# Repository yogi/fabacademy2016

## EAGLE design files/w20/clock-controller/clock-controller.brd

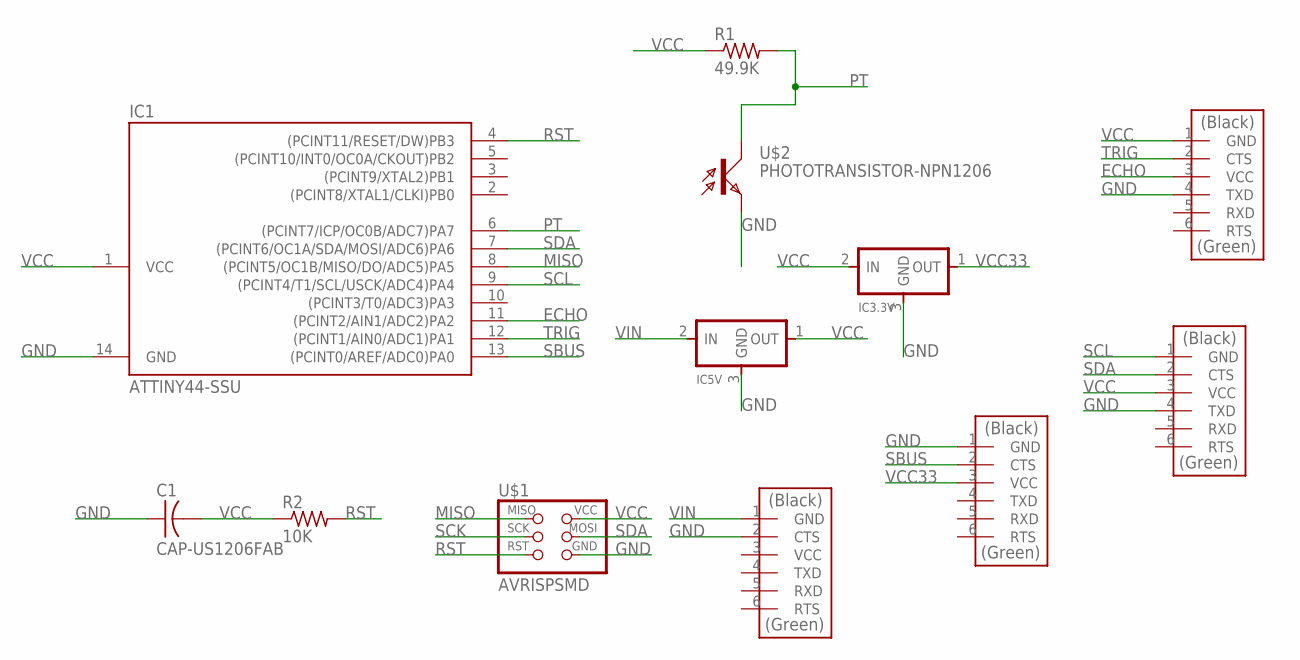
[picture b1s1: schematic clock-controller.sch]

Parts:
C1: CAP-US1206FAB; C1206FAB
DIGITS: FTDI-SMD-HEADER; 1X06SMD
IC1: ATTINY44-SSU; SOIC14
IC3.3V, IC5V: REGULATORSOT23; SOT23
R1: 49.9K; R1206FAB
R2: 10K; R1206FAB
RTC: FTDI-SMD-HEADER; 1X06SMD
U$1: AVRISPSMD; 2X03SMD
U$2: PHOTOTRANSISTOR-NPN1206; OP1206
ULTRA: FTDI-SMD-HEADER; 1X06SMD
USB: FTDI-SMD-HEADER; 1X06SMD

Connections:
ECHO: IC1.11 ((PCINT2/AIN1/ADC2)PA2), ULTRA.3 (VCC)
GND: C1.1, DIGITS.1 (GND), IC1.14 (GND), IC3.3V.3 (GND), IC5V.3 (GND), RTC.4 (TXD), U$1.6 (GND), U$2.EMITTER (E), ULTRA.4 (TXD), USB.2 (CTS)
MISO: IC1.8 ((PCINT5/OC1B/MISO/DO/ADC5)PA5), U$1.1 (MISO)
PT: IC1.6 ((PCINT7/ICP/OC0B/ADC7)PA7), R1.2, U$2.COLLECTOR (C)
RST: IC1.4 ((PCINT11/RESET/DW)PB3), R2.2, U$1.5 (RST)
SBUS: DIGITS.2 (CTS), IC1.13 ((PCINT0/AREF/ADC0)PA0)
SCK: U$1.3 (SCK)
SCL: IC1.9 ((PCINT4/T1/SCL/USCK/ADC4)PA4), RTC.1 (GND)
SDA: IC1.7 ((PCINT6/OC1A/SDA/MOSI/ADC6)PA6), RTC.2 (CTS), U$1.4 (MOSI)
TRIG: IC1.12 ((PCINT1/AIN0/ADC1)PA1), ULTRA.2 (CTS)
VCC: C1.2, IC1.1 (VCC), IC3.3V.2 (IN), IC5V.1 (OUT), R1.1, R2.1, RTC.3 (VCC), U$1.2 (VCC), ULTRA.1 (GND)
VCC33: DIGITS.3 (VCC), IC3.3V.1 (OUT)
VIN: IC5V.2 (IN), USB.1 (GND)

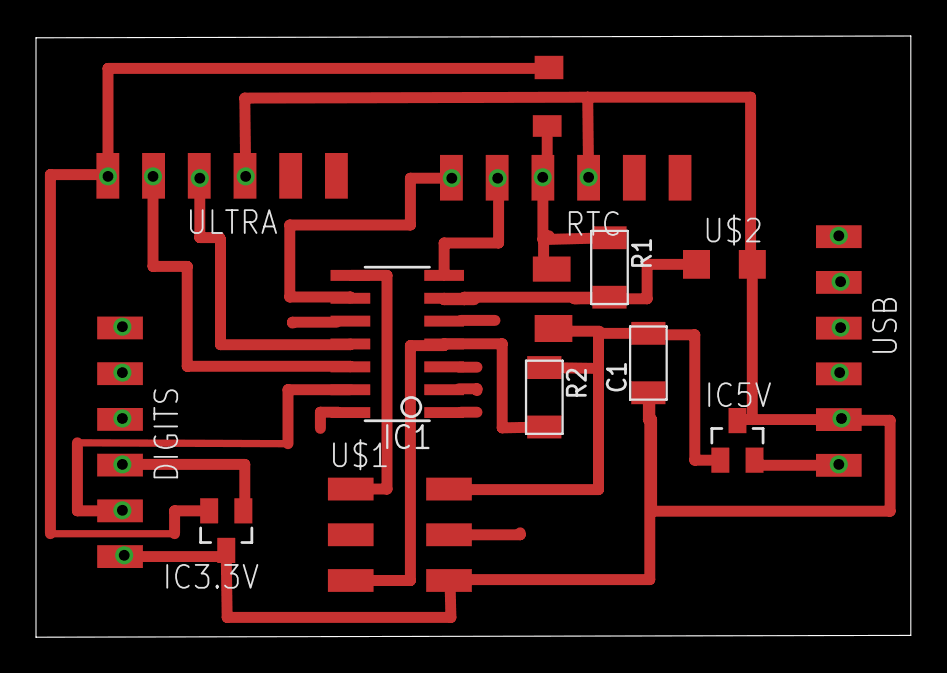
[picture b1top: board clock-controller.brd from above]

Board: 2 copper layers, 48.6 x 33.4 mm, 12 parts (0 on the bottom side), 12 nets.

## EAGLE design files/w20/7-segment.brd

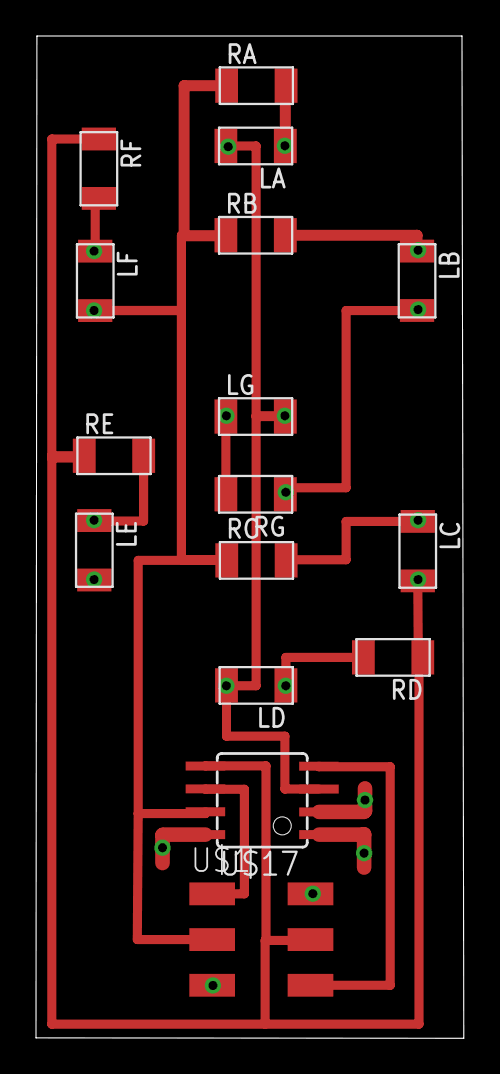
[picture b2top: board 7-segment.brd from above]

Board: 2 copper layers, 23.8 x 55.7 mm, 16 parts (0 on the bottom side), 15 nets.

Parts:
LA: LEDFAB1206; LED1206FAB
LB: LEDFAB1206; LED1206FAB
LC: LEDFAB1206; LED1206FAB
LD: LEDFAB1206; LED1206FAB
LE: LEDFAB1206; LED1206FAB
LF: LEDFAB1206; LED1206FAB
LG: LEDFAB1206; LED1206FAB
RA: R1206FAB
RB: R1206FAB
RC: R1206FAB
RD: R1206FAB
RE: R1206FAB
RF: R1206FAB
RG: R1206FAB
U$1: AVRISPSMD; 2X03SMD
U$17: ATTINY45SI; SOIC8

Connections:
GND: U$1.6, U$17.4
MISO: U$1.1, U$17.6
MOSI: LC.2, RD.1, RE.1, RF.1, U$1.4, U$17.5
unnamed: LA.1, RA.2
unnamed: LB.1, RB.2
unnamed: LC.1, RC.2
unnamed: LD.1, RD.2
unnamed: LE.1, RE.2
unnamed: LF.1, RF.2
unnamed: LG.1, RG.2
PB3: LB.2, LE.2, RG.1, U$17.2
PB4: LA.2, LD.2, LG.2, U$17.3
RST: U$1.5, U$17.1
SCK: LF.2, RA.1, RB.1, RC.1, U$1.3, U$17.7
VCC: U$1.2, U$17.8

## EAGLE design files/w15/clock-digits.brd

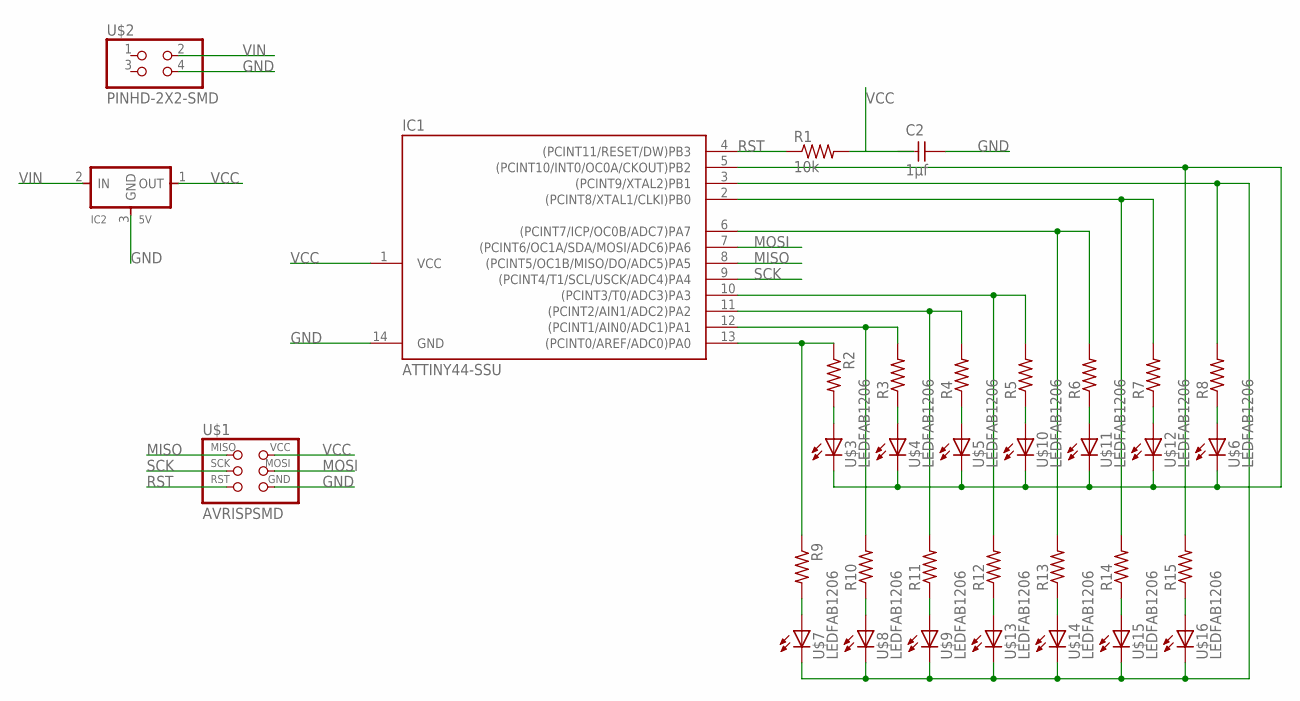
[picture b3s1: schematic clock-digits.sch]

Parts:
C2: 1µf; C1206FAB
IC1: ATTINY44-SSU; SOIC14
IC2: 5V; SOT23
R1: 10k; R1206FAB
R2, R3, R4, R5, R6, R7, R8, R9, R10, R11, R12, R13, R14, R15: RES-US1206FAB; R1206FAB
U$1: AVRISPSMD; 2X03SMD
U$2: PINHD-2X2-SMD; 2X02SMD
U$3, U$4, U$5, U$6, U$7, U$8, U$9, U$10, U$11, U$12, U$13, U$14, U$15, U$16: LEDFAB1206; LED1206FAB

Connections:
GND: C2.2, IC1.14 (GND), IC2.3 (GND), U$1.6 (GND), U$2.4
MISO: IC1.8 ((PCINT5/OC1B/MISO/DO/ADC5)PA5), U$1.1 (MISO)
MOSI: IC1.7 ((PCINT6/OC1A/SDA/MOSI/ADC6)PA6), U$1.4 (MOSI)
unnamed: IC1.13 ((PCINT0/AREF/ADC0)PA0), R2.1, R9.1
unnamed: R2.2, U$3.1 (A)
unnamed: IC1.12 ((PCINT1/AIN0/ADC1)PA1), R3.2, R10.2
unnamed: R3.1, U$4.1 (A)
unnamed: IC1.11 ((PCINT2/AIN1/ADC2)PA2), R4.2, R11.2
unnamed: R4.1, U$5.1 (A)
unnamed: IC1.10 ((PCINT3/T0/ADC3)PA3), R5.2, R12.2
unnamed: R5.1, U$10.1 (A)
unnamed: IC1.6 ((PCINT7/ICP/OC0B/ADC7)PA7), R6.2, R13.2
unnamed: R6.1, U$11.1 (A)
unnamed: IC1.2 ((PCINT8/XTAL1/CLKI)PB0), R7.2, R14.2
unnamed: R7.1, U$12.1 (A)
unnamed: R8.1, U$6.1 (A)
unnamed: IC1.5 ((PCINT10/INT0/OC0A/CKOUT)PB2), R15.2, U$3.2 (C), U$4.2 (C), U$5.2 (C), U$6.2 (C), U$10.2 (C), U$11.2 (C), U$12.2 (C)
unnamed: R9.2, U$7.1 (A)
unnamed: R15.1, U$16.1 (A)
unnamed: R10.1, U$8.1 (A)
unnamed: R11.1, U$9.1 (A)
unnamed: R12.1, U$13.1 (A)
unnamed: R13.1, U$14.1 (A)
unnamed: R14.1, U$15.1 (A)
unnamed: IC1.3 ((PCINT9/XTAL2)PB1), R8.2, U$7.2 (C), U$8.2 (C), U$9.2 (C), U$13.2 (C), U$14.2 (C), U$15.2 (C), U$16.2 (C)
RST: IC1.4 ((PCINT11/RESET/DW)PB3), R1.1, U$1.5 (RST)
SCK: IC1.9 ((PCINT4/T1/SCL/USCK/ADC4)PA4), U$1.3 (SCK)
VCC: C2.1, IC1.1 (VCC), IC2.1 (OUT), R1.2, U$1.2 (VCC)
VIN: IC2.2 (IN), U$2.2

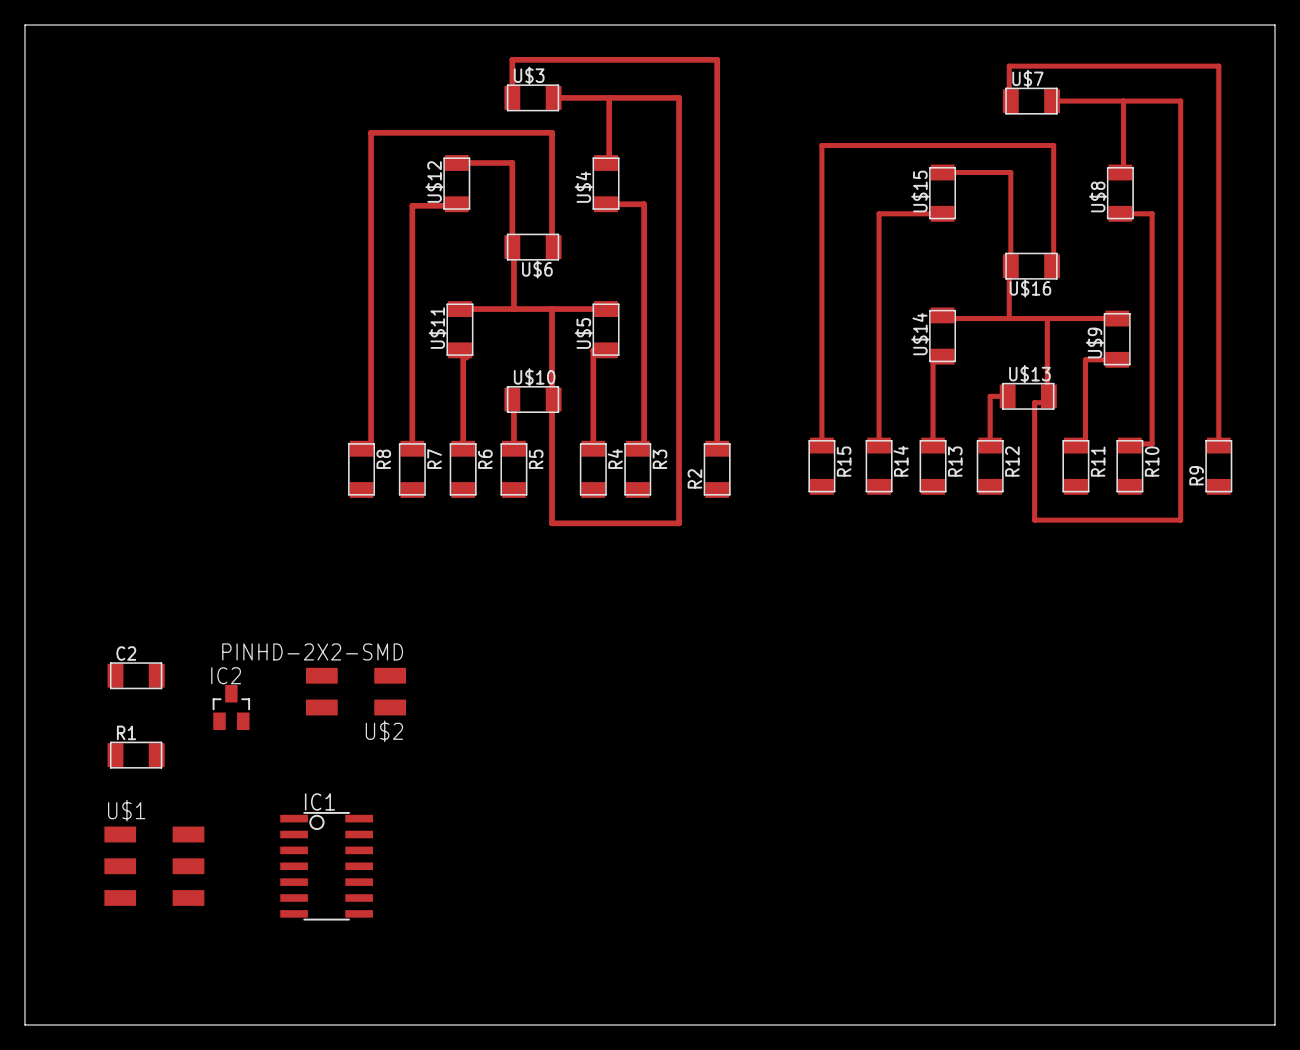
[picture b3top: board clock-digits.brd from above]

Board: 2 copper layers, 100.0 x 80.0 mm, 34 parts (0 on the bottom side), 29 nets.

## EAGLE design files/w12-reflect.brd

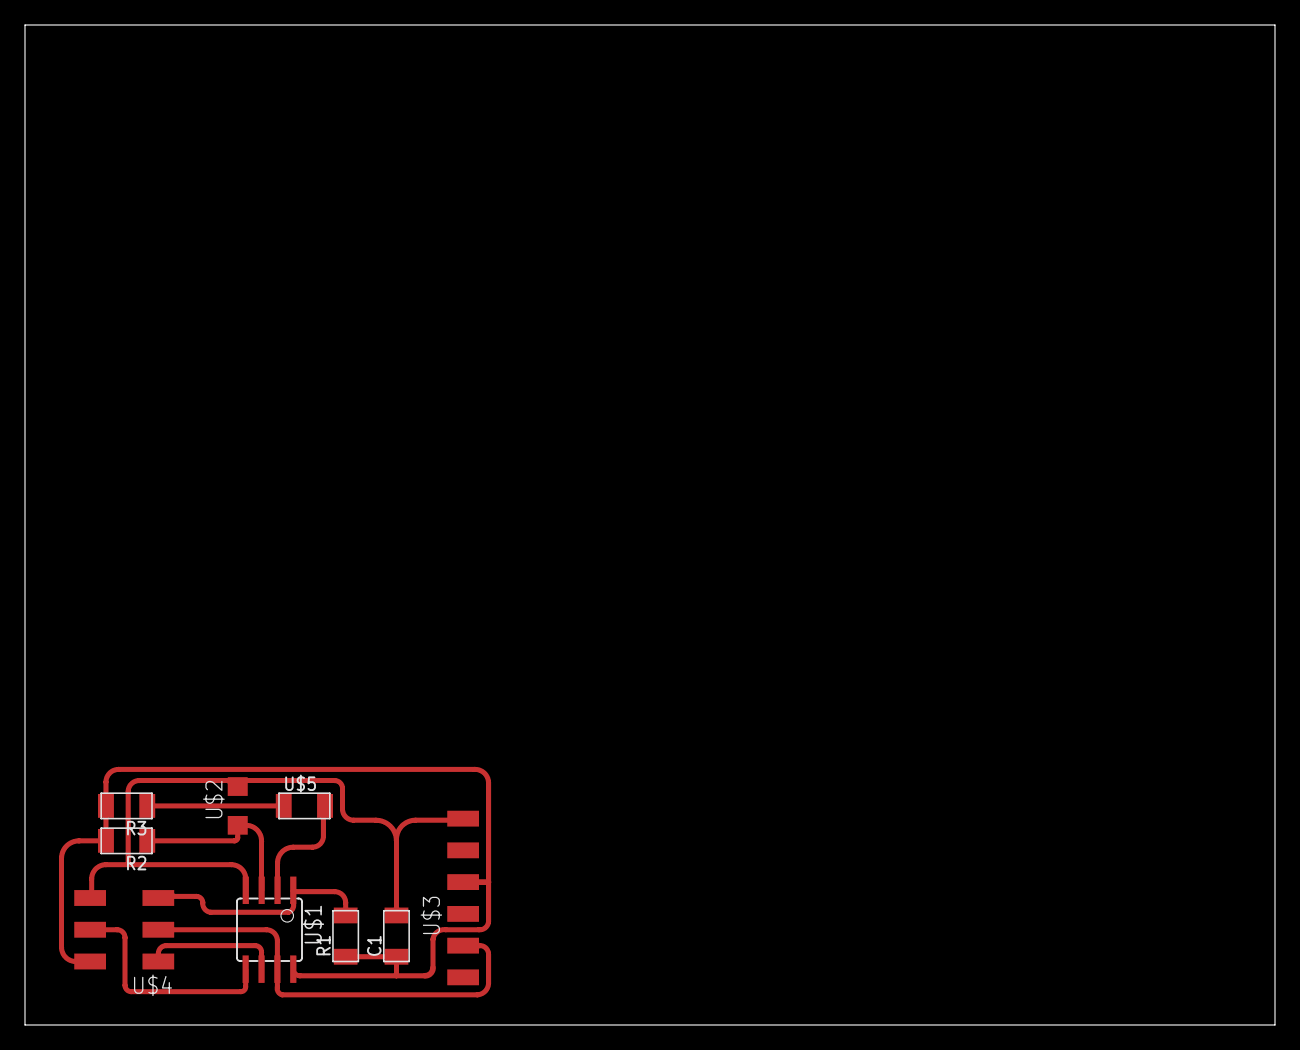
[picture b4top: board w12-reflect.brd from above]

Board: 2 copper layers, 100.0 x 80.0 mm, 9 parts (0 on the bottom side), 9 nets.

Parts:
C1: CAP-US1206FAB; C1206FAB
R1: 10k; R1206FAB
R2: 49.9k; R1206FAB
R3: 1k; R1206FAB
U$1: ATTINY45SI; SOIC8
U$2: PHOTOTRANSISTOR-NPN1206; OP1206
U$3: FTDI-SMD-HEADER; 1X06SMD
U$4: AVRISPSMD; 2X03SMD
U$5: LEDFAB1206; LED1206FAB

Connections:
GND: C1.2, U$1.4, U$2.EMITTER, U$3.1, U$4.6
LED: U$1.2, U$5.2
MISO: U$1.6, U$4.1
MOSI: U$1.5, U$4.4
unnamed: R3.1, U$5.1
PT: R2.1, U$1.3, U$2.COLLECTOR
RST: R1.2, U$1.1, U$4.5
SCK: U$1.7, U$3.5, U$4.3
VCC: C1.1, R1.1, R2.2, R3.2, U$1.8, U$3.3, U$4.2

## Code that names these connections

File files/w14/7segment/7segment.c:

#include <avr/io.h>
#include <util/delay.h>

#define SCK_PIN PB2
#define MOSI_PIN PB0

#define ABC_ANODE   SCK_PIN
#define A           PB4
#define B           PB3
#define C           MOSI_PIN

#define DEF_ANODE   MOSI_PIN
#define D           PB4
#define E           PB3
#define F           SCK_PIN

#define G_ANODE     PB3
#define G           PB4

#define DIR_REG   DDRB

#define output(pin) (DIR_REG |= (1 << pin)) // set port direction for output
#define input(pin) (DIR_REG &= (~ (1 << pin))) // set port direction for input
#define set(pin) (PORTB |= (1 << pin)) // set port pin
#define clear(pin) (PORTB &= (~ (1 << pin))) // clear port pin

const int FLICKER_DELAY_MS = 100;
const int DIGIT_DELAY_MS = 5000;

char DIGIT_SEGMENTS[10][7] = {
     {'A', 'B', 'C', 'D', 'E', 'F'},            // 0
     {'B', 'C'},                                // 1
     {'A', 'B', 'D', 'E', 'G'},                 // 2
     {'A', 'B', 'C', 'D', 'G'},                 // 3
     {'B', 'C', 'F', 'G'},                      // 4
     {'A', 'C', 'D', 'F', 'G'},                 // 5
     {'A', 'C', 'D', 'E', 'F', 'G'},            // 6
     {'A', 'B', 'C'},                           // 7
     {'A', 'B', 'C', 'D', 'E', 'F', 'G',},      // 8
     {'A', 'B', 'C', 'F', 'G',}                 // 9
};

int DIGIT_NUM_SEGMENTS[] = {
    6, // 0
    2, // 1
    5, // 2
    5, // 3
    4, // 4
    5, // 5
    6, // 6
    3, // 7
    7, // 8
    5  // 9
};

int anode_pin_for(char led) {
    if (led == 'A' || led == 'B' || led == 'C') 
        return ABC_ANODE;
    else if (led == 'D' || led == 'E' || led == 'F') 
        return DEF_ANODE;
    else  
        return G_ANODE;
}

int led_pin_for(char led) {
    if (led == 'A' || led == 'D' || led == 'G')
        return PB4;
    else if (led == 'B' || led == 'E')
        return PB3;
    else if (led == 'C')
        return MOSI_PIN;
    else // 'F'
        return SCK_PIN;
}

void high_impedance(pin) {
    input(pin);
    clear(pin);
}

void flash(char led) {
    int anode_pin = anode_pin_for(led);
    int led_pin = led_pin_for(led);
    
    output(anode_pin);    
    output(led_pin);
        
    set(anode_pin);
    clear(led_pin);

    _delay_ms(FLICKER_DELAY_MS);
    
    high_impedance(anode_pin);    
    high_impedance(led_pin);
}

void flicker(char segments[]) {
    int i;
    int len = sizeof(segments) / sizeof(char);
    for (i = 0; i < len; i++) {
        flash(segments[i]);
    }
}

void display(int digit) {
    int i;
    char *segments = DIGIT_SEGMENTS[digit];
    int num_segments = DIGIT_NUM_SEGMENTS[digit];
//    int cycles = DIGIT_DELAY_MS / (FLICKER_DELAY_MS * num_segments);
    int cycles = DIGIT_DELAY_MS / (FLICKER_DELAY_MS * 2);
    for (i = 0; i < cycles; i++) {
        flicker(segments);
    }
}

/*
int main(void) {
    high_impedance(PB0);
    high_impedance(PB1);
    high_impedance(PB2);
    high_impedance(PB3);
    high_impedance(PB4);

    int i = 0;
    while(1) {
        display(i); 
        if (++i >= 10)
            i = 0;
    }
    
    return 0;
}
*/


int main(void) {
    char leds[] = {'A', 'B', 'C', 'D', 'E', 'F', 'G'};
    int i = 0;
    
    while(1) {
        flash(leds[i++]);
        _delay_ms(100);
        if (i >= 7)
            i = 0;
    }
    
    return 0;
}

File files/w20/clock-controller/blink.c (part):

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
#define digit_bus_port PORTA
#define digit_bus_direction DDRA
#define digit_bus_pin_out (1 << PA0)

#define serial_port PORTB
#define serial_direction DDRB
#define serial_pin_out (1 << PB2)

#define trigger_port PORTA
#define trigger_direction DDRA
#define trigger_pin_out (1 << PA1)

#define echo_port PORTA
#define echo_direction DDRA
#define echo_pin_in (1 << PA2)
#define echo_pins PINA

#define TURN_OFF_DISPLAY 11
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
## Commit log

2016-03-11 import from git.fabacademy.org
2016-03-11 add link in footer to site source on github
2016-03-14 machining notes
2016-03-14 table design in rhino
2016-03-14 zip 3dm file, which reduces size by 99%!
2016-03-14 fix zip folder
2016-03-14 zip big files
2016-03-15 scaled down model
2016-03-15 table done
2016-03-15 w8 page
2016-03-16 allowance offset note
2016-03-16 fix links
2016-03-17 w8 blink led
2016-03-17 update w4 notes
2016-03-17 update notes
2016-03-17 using my isp
2016-03-17 move blink.ino to its folder
2016-03-17 change title
2016-03-19 button + LED
2016-03-19 c blink led program
2016-03-20 c led program
2016-03-21 datasheet review notes
2016-03-21 fix headings
2016-03-21 assembler test
2016-03-21 original files links
2016-03-22 minor edits
2016-03-22 assembly blink program with delay
2016-03-22 program size comparisons
2016-03-22 interrupt-based program
2016-03-22 remove Todo
2016-03-23 polishing
2016-03-23 w10 page created
2016-03-23 floating menu
2016-03-23 intro
2016-03-23 about page
2016-03-29 timer blink
2016-03-29 tweaks
2016-03-29 refactor
2016-04-11 complete notes on uart
2016-04-11 remove *.elf and *.o files
2016-04-11 include uart section in index
2016-04-11 remove questions
2016-04-12 added w11 page
2016-04-15 fix machine index pic
2016-04-15 added combined machine page
2016-04-15 machine notes
2016-04-16 created w12-input
2016-04-17 schematic and board
2016-04-18 traces and outline png
2016-04-18 board done
2016-04-18 inputs hero shot
2016-04-20 theme refactoring - index page done
2016-04-20 theme refactoring - fix navbar
2016-04-20 index re-theming done
2016-04-20 footer
2016-04-22 fix format errors on all pages
2016-04-22 change navbar text color
2016-04-22 add photo
2016-04-22 fix layout
2016-04-22 minor tweaks to fabacademy page
2016-04-22 fix link
2016-04-25 added w13 page, fixed navbar toggle for small screens
2016-04-26 spirograph rhino design
2016-04-26 spirograph mold designs
2016-04-26 gear test mold
2016-04-26 mold milled
2016-04-26 updated index, added rhino files zip
2016-04-27 silicone mold casting
2016-04-27 spirograph casting
2016-04-29 output devices page created
2016-05-02 clock digits schematic
2016-05-02 board routing
2016-05-02 first digit routed internally
2016-05-02 2nd digit routed
2016-05-03 starting on 7-digit module
2016-05-03 fixed folder name
2016-05-03 7segment schematic done
2016-05-03 board placed
2016-05-03 routing in progress
2016-05-03 schematic without ISP header done
2016-05-04 board programmed
2016-05-04 added video
2016-05-04 fix note
2016-05-05 leds working fine
2016-05-05 digit display logic
2016-05-10 fix index link
2016-05-11 led digits done
2016-05-11 digits animated gif
2016-05-11 add links to original files
2016-05-11 add code
2016-05-11 added all index links
2016-05-11 composites delay note
2016-05-11 final project notes
2016-05-11 final project planning
2016-05-12 clock: test digit laser cut
2016-05-13 ultrasonic sensor test
2016-05-13 rtc test
2016-05-14 test cuts
2016-05-15 board layout done with resistors and LED positions swapped
2016-05-15 board layout tweaks
2016-05-15 vias done
2016-05-16 7-segment programmed
2016-05-18 notes
2016-05-18 i2c prototype
2016-05-23 simple i2c request working
2016-05-23 i2 slave response
2016-05-23 added original file links
2016-05-23 update index page
2016-05-25 late note
2016-05-31 7segment board refactoring
2016-06-01 new bpard programmed
2016-06-01 arduino -> 7segment interaction
2016-06-02 interrupt based serial io
2016-06-02 basic serial comm with blocking get_char working
2016-06-02 ISR working
2016-06-02 interrupt-based serial reads finally working
2016-06-08 board production
2016-06-09 board production notes
2016-06-09 w17 hello world
2016-06-09 hello world chrome app
2016-06-09 js displaying values
2016-06-11 create js files
2016-06-11 aviator scene with sensor input
2016-06-11 update index
2016-06-12 added rocket
2016-06-12 rename
2016-06-13 update code, images, video
2016-06-13 fix variable names
2016-06-13 added source zip
2016-06-15 syntax highlighting of code
2016-06-16 fix boards
2016-06-16 makefile for i2c
2016-06-17 starting on digits firmware
2016-06-20 get digits serial comm working
2016-06-20 fixed digit bus noise
2016-06-20 reformat
2016-06-20 RTC interaction
2016-06-21 rename vars
2016-06-21 print debugging output
2016-06-21 ADC fixed
2016-06-21 turn off display when dark
2016-06-21 added presentation.png
2016-06-21 move presentation.png to root folder
2016-06-22 phototransistor working!
2016-06-22 clean up
2016-06-22 ultrasonic working
2016-06-22 clean up code
2016-06-22 presentation.mp4
2016-06-22 presentation.png
2016-07-03 final check in
2022-04-17 setup dev env
